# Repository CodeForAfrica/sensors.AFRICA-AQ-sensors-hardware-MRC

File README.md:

# sensors.AFRICA MRC AQ Kits Hardware

## Tools used

* Autodesk Eagle

* Fusion360

## sensors.AFRICA Stack

1. Firmware - https://github.com/CodeForAfrica/sensors.AFRICA-AQ-sensors-software
2. API - https://github.com/CodeForAfricaLabs/sensors.AFRICA-AQ-api
3. Map - https://github.com/CodeForAfrica/sensors.AFRICA-AQ-map-v2

## Documentation

The Documentation is under development.

## License

GNU General Public License v3.0

sensors.AFRICA is a citizen-science focused project by Code for Africa that seeks to address data gaps by providing low cost sensors, which people can use to measure and monitor the quality of the air, water, and environment in their communities. This web app seeks to be the public portal through which most users would discover and explore the data and intiative.

Copyright (C) 2019 Code for Africa

This program is free software: you can redistribute it and/or modify
it under the terms of the GNU General Public License as published by
the Free Software Foundation, either version 3 of the License, or
(at your option) any later version.

This program is distributed in the hope that it will be useful,
but WITHOUT ANY WARRANTY; without even the implied warranty of
MERCHANTABILITY or FITNESS FOR A PARTICULAR PURPOSE. See the
GNU General Public License for more details.

You should have received a copy of the GNU General Public License
along with this program. If not, see <https://www.gnu.org/licenses/>

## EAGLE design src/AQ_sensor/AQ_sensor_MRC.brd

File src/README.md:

# sensors.AFRICA / MRC AQ sensors hardware

This folder contains the Eagle design files for the sensors.AFRICA MRC boards.

### Folders

* **AQ_sensor** The Printed Circuit Board of the AQ kit

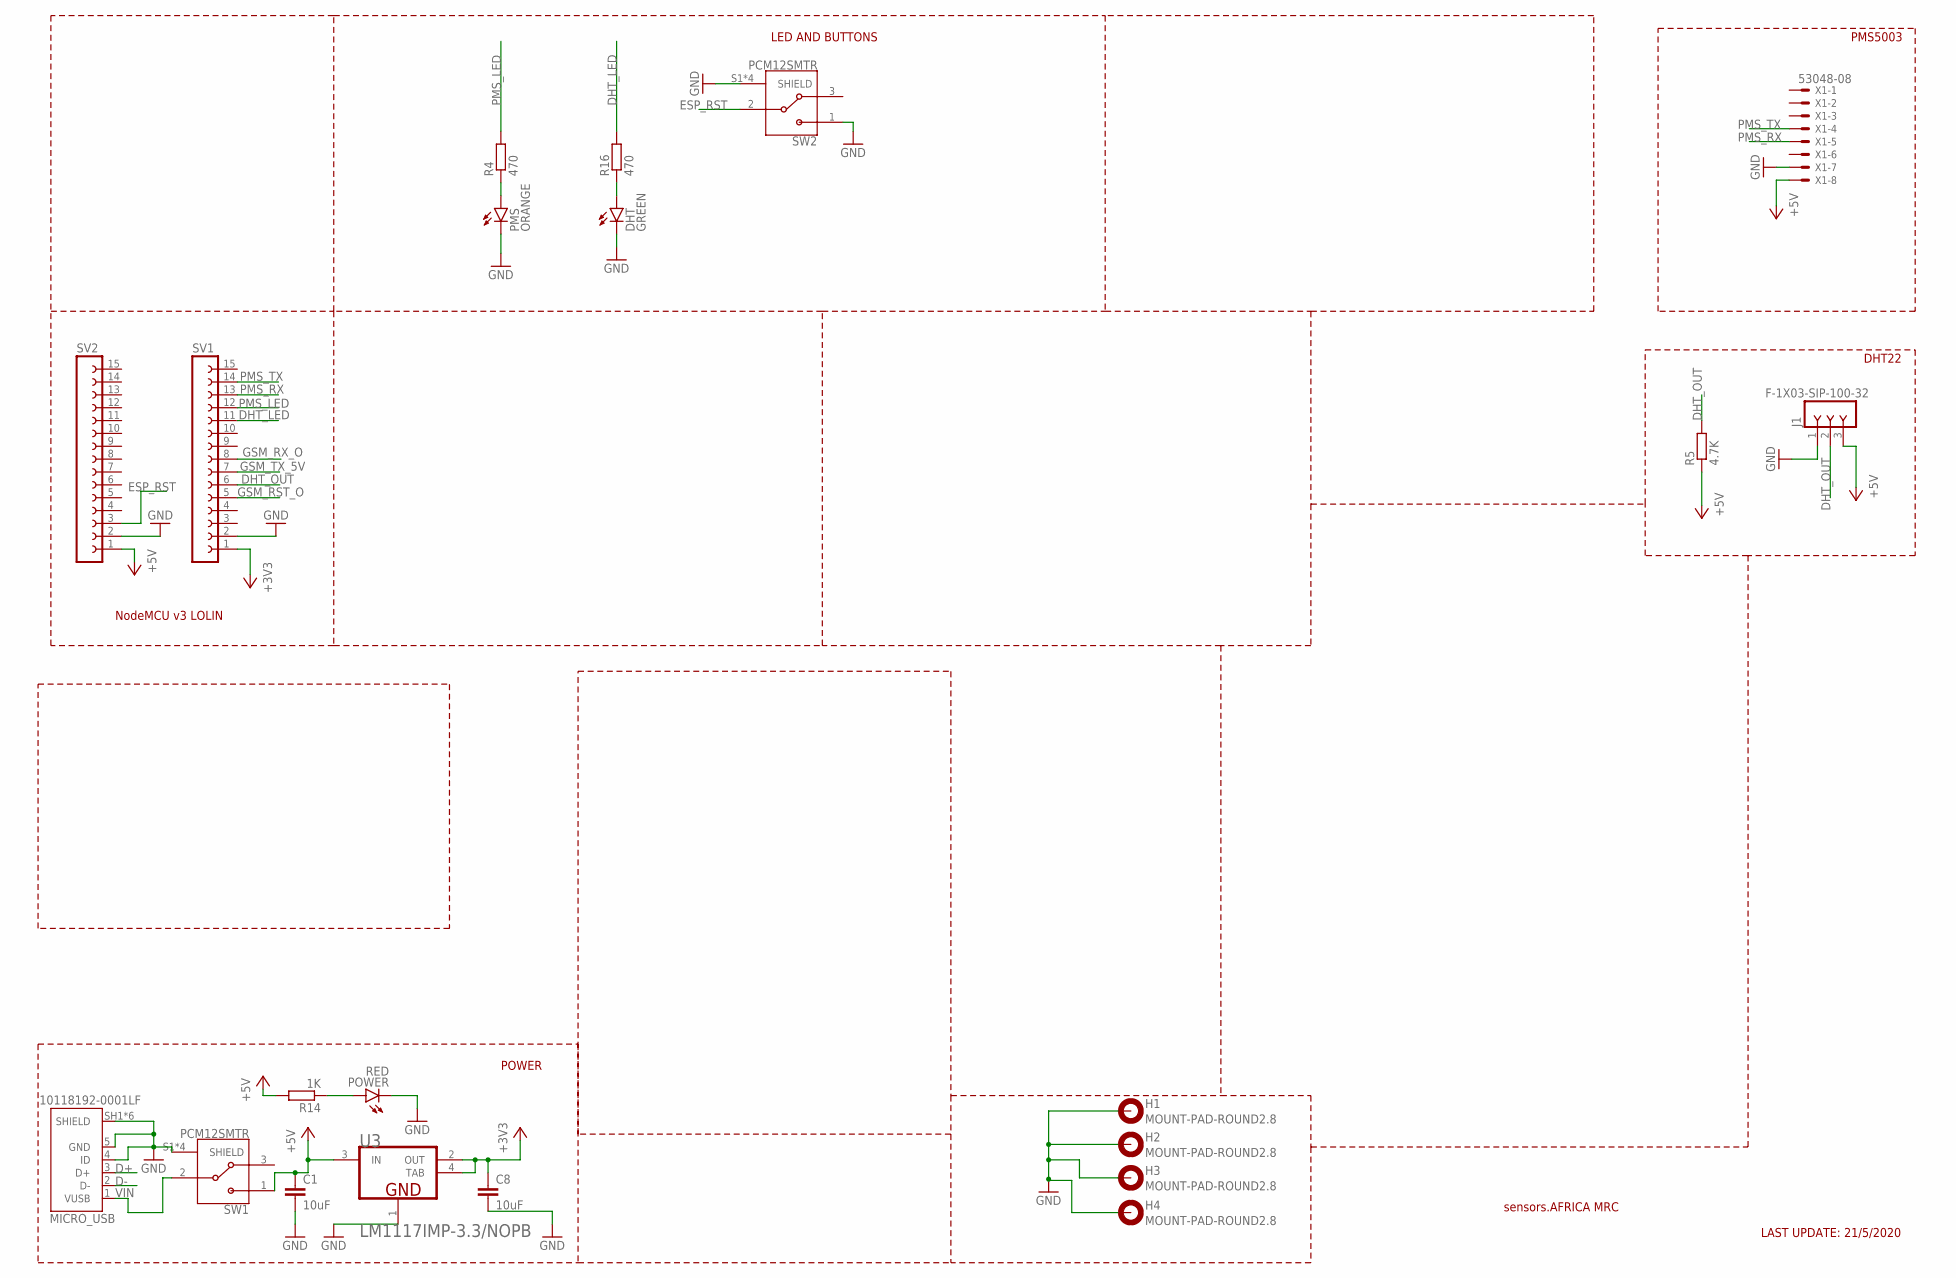
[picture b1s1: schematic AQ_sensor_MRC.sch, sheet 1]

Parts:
C1, C8: 10uF; C0603
DHT: GREEN; CHIP-LED0603
H1, H2, H3, H4: MOUNT-PAD-ROUND2.8; 2,8-PAD
J1: F-1X03-SIP-100-32; SIP-100-03-32
MICRO_USB: 10118192-0001LF; AMPHENOL_10118192-0001LF
PMS: ORANGE; CHIP-LED0603
POWER: RED; CHIP-LED0603
R4, R16: 470; R0603
R5: 4.7K; R0603
R14: 1K; R0603
SV1, SV2: FE15-1; FE15
SW1, SW2: PCM12SMTR; SW_PCM12SMTR
U3: TEXAS_INSTRUMENTS_LM1117IMP-3.3-NOPBTEXAS_INSTRUM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; TEXAS_INSTRUMENTS_LM1117IMP-3.3-NOPB_0
X1: 53048-08

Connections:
+3V3: C8.1, SV1.1, U3.2 (OUT), U3.4 (TAB)
+5V: C1.1, J1.3, R5.1, R14.2, SV2.1, SW1.1, U3.3 (IN), X1.8; also elsewhere on the board
D+: MICRO_USB.3 (D+)
D-: MICRO_USB.2 (D-)
DHT_LED: R16.2, SV1.11
DHT_OUT: J1.2, R5.2, SV1.6
ESP_RST: SV2.3, SW2.2
GND: C1.2, C8.2, DHT.C, H1.B2,8, H2.B2,8, H3.B2,8, H4.B2,8, J1.1, MICRO_USB.4 (ID), MICRO_USB.5 (GND), MICRO_USB.SH1 (SHIELD), MICRO_USB.SH2 (SHIELD), MICRO_USB.SH3 (SHIELD), MICRO_USB.SH4 (SHIELD), MICRO_USB.SH5 (SHIELD), MICRO_USB.SH6 (SHIELD), PMS.C, POWER.C, SV1.2, SV2.2, SW1.S1 (SHIELD), SW1.S2 (SHIELD), SW1.S3 (SHIELD), SW1.S4 (SHIELD), SW2.1, SW2.S1 (SHIELD), SW2.S2 (SHIELD), SW2.S3 (SHIELD), SW2.S4 (SHIELD), U3.1 (GND), X1.7; also elsewhere on the board
GSM_RST_O: SV1.5; also elsewhere on the board
GSM_RX_O: SV1.8; also elsewhere on the board
GSM_TX_5V: SV1.7; also elsewhere on the board
unnamed: PMS.A, R4.1
unnamed: POWER.A, R14.1
unnamed: DHT.A, R16.1
PMS_LED: R4.2, SV1.12
PMS_RX: SV1.13, X1.5
PMS_TX: SV1.14, X1.4
VIN: MICRO_USB.1 (VUSB), SW1.2

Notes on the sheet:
sensors.AFRICA MRC
LAST UPDATE: 21/5/2020
LED AND BUTTONS
PMS5003
DHT22
NodeMCU v3 LOLIN
POWER

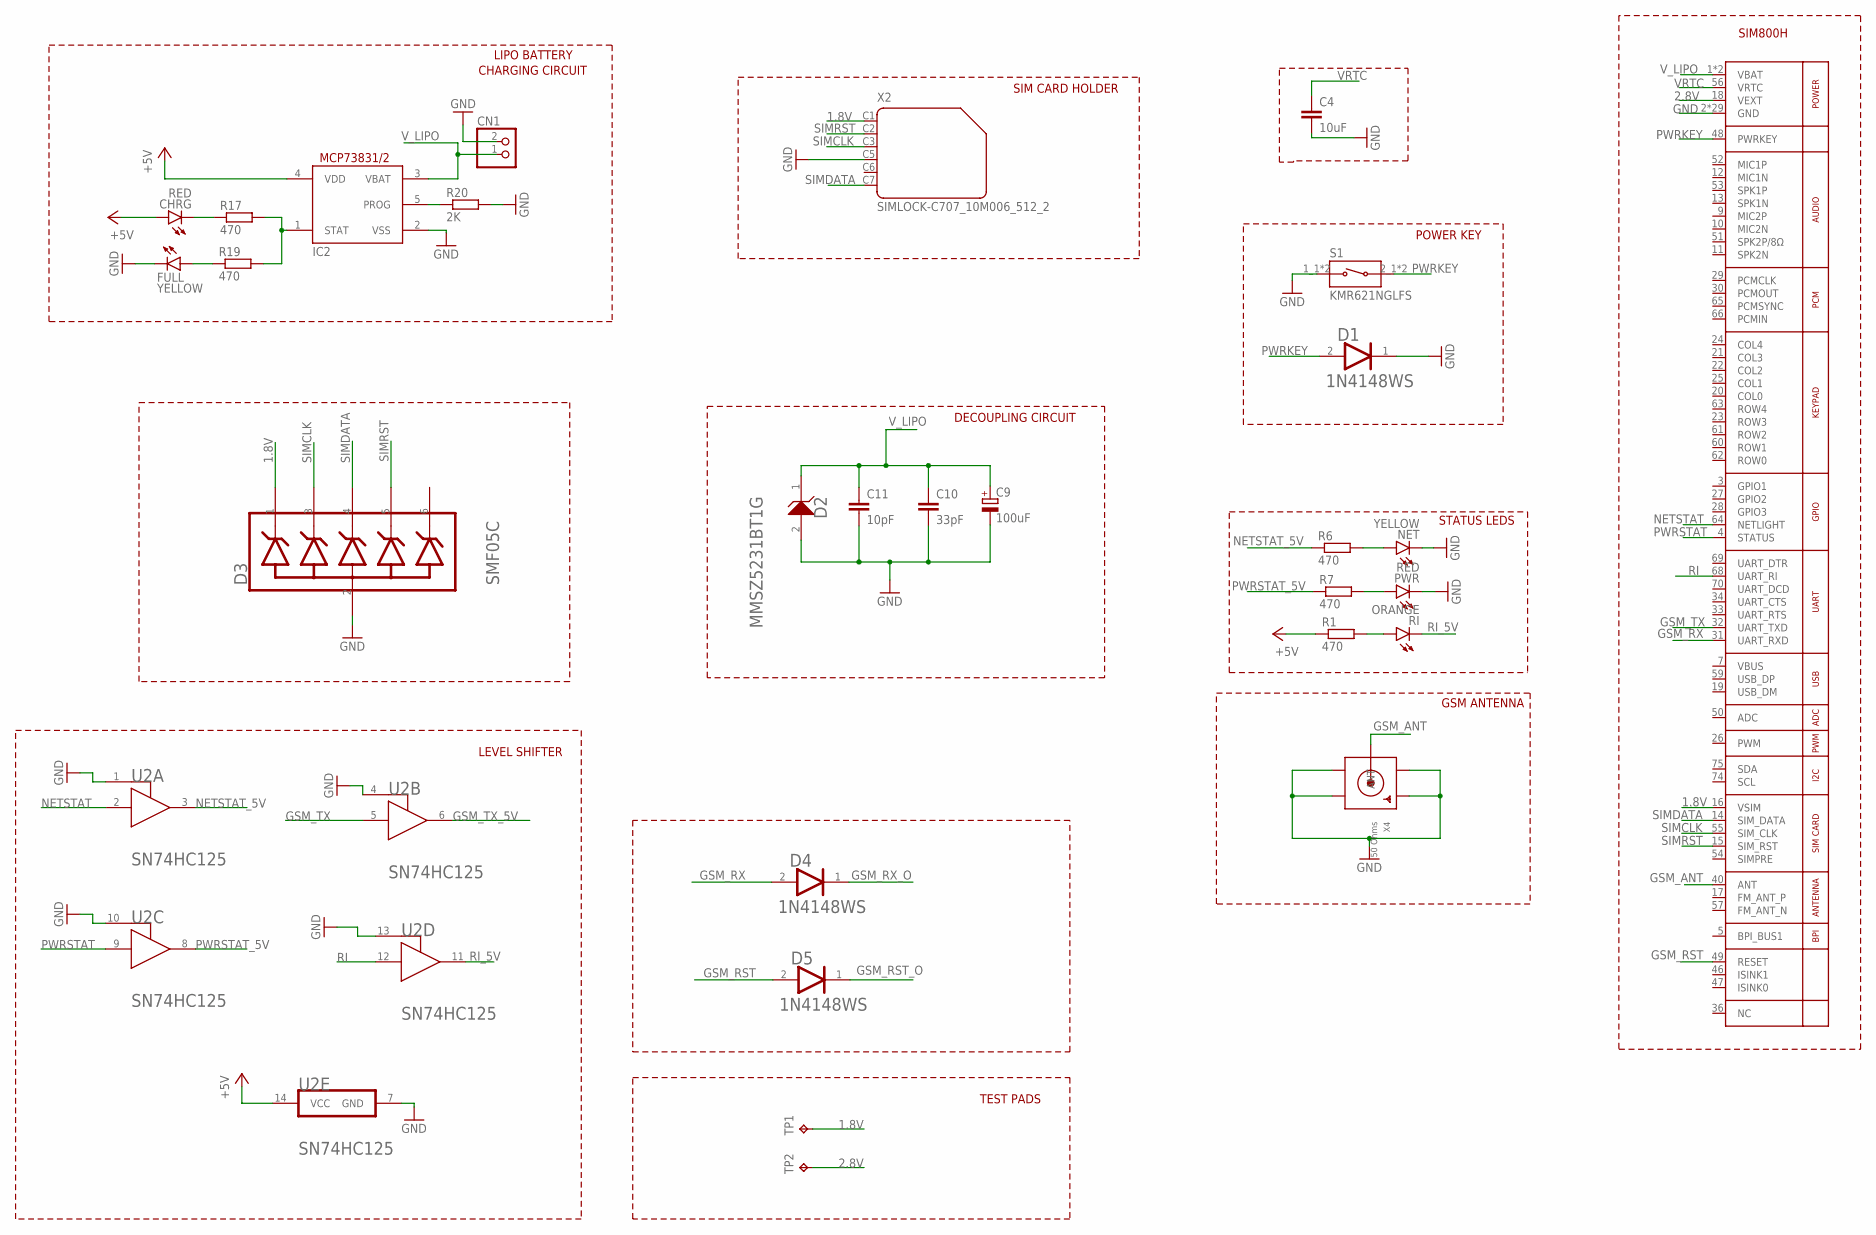
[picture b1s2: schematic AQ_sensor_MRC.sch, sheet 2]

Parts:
C4: 10uF; C0603
C9: 100uF; PANASONIC_D
C10: 33pF; C0603
C11: 10pF; C0603
CHRG: RED; CHIP-LED0603
CN1: JST_2PIN-SMT-RA; JST-PH-2-SMT-RA
D1, D4, D5: ON_SEMI_1N4148WSON_SEMI_1N4148WS_0_0; ON_SEMI_1N4148WS_0
D2: ON_SEMICONDUCTOR_MMSZ5231BT1GON_SEMICONDUCTOR_MMS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; ON_SEMICONDUCTOR_MMSZ5231BT1G_0
D3: SEMTECH_SMF05CSEMTECH_SMF05C_0_0; SEMTECH_SMF05C_0
FULL: YELLOW; CHIP-LED0603
IC2: MCP73831/OT; SOT23-5L
NET: YELLOW; CHIP-LED0603
PWR: RED; CHIP-LED0603
R1, R6, R7, R17, R19: 470; R0603
R20: 2K; R0603
RI: ORANGE; CHIP-LED0603
S1: KMR621NGLFS; SW_KMR621NGLFS
TP1, TP2: TPB1,27; B1,27
U1: GSM_SIM800L; SIM800L
U2: TEXAS_INSTRUMENTS_SN74HC125TEXAS_INSTRUMENTS_SN74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; TEXAS_INSTRUMENTS_SN74HC125_0
X2: SIMLOCK-C707_10M006_512_2; C707_10M006_512_2
X4: 50 Ohms; SMA_EDGELAUNCH_UFL

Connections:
1.8V: D3.1 (1_CATHODE), TP1.TP, U1.16 (VSIM), X2.C1 (1)
2.8V: TP2.TP, U1.18 (VEXT)
+5V: CHRG.A, IC2.4 (VDD), R1.1, U2.14 (VCC); also elsewhere on the board
GND: C4.2, C9.-, C10.2, C11.2, CN1.2 (1), D1.1 (CATHODE), D2.2 (A), D3.2 (ANODE), FULL.C, IC2.2 (VSS), NET.C, PWR.C, R20.2, S1.1_1 (1), S1.1_2 (1), U1.2 (GND), U1.6 (GND), U1.8 (GND), U1.35 (GND), U1.37 (GND), U1.38 (GND), U1.39 (GND), U1.41 (GND), U1.43 (GND), U1.44 (GND), U1.45 (GND), U1.58 (GND), U1.67 (GND), U1.71 (GND), U1.72 (GND), U1.73 (GND), U1.76 (GND), U1.77 (GND), U1.78 (GND), U1.79 (GND), U1.80 (GND), U1.81 (GND), U1.82 (GND), U1.83 (GND), U1.84 (GND), U1.85 (GND), U1.86 (GND), U1.87 (GND), U1.88 (GND), U2.1 (1_!OE!), U2.4 (4_!OE!), U2.7 (GND), U2.10 (2_!OE!), U2.13 (3_!OE!), X2.C5 (4), X4.GND@1 (GND1), X4.GND@2 (GND2), X4.GND@3 (GND3), X4.GND@4 (GND4); also elsewhere on the board
GSM_ANT: U1.40 (ANT), X4.P (ANT)
GSM_RST: D5.2 (ANODE), U1.49 (RESET)
GSM_RST_O: D5.1 (CATHODE); also elsewhere on the board
GSM_RX: D4.2 (ANODE), U1.31 (UART_RXD)
GSM_RX_O: D4.1 (CATHODE); also elsewhere on the board
GSM_TX: U1.32 (UART_TXD), U2.5 (2A)
GSM_TX_5V: U2.6 (2Y); also elsewhere on the board
unnamed: CHRG.C, R17.1
unnamed: IC2.1 (STAT), R17.2, R19.2
unnamed: NET.A, R6.2
unnamed: PWR.A, R7.2
unnamed: FULL.A, R19.1
unnamed: IC2.5 (PROG), R20.1
unnamed: R1.2, RI.A
NETSTAT: U1.64 (NETLIGHT), U2.2 (1A)
NETSTAT_5V: R6.1, U2.3 (1Y)
PWRKEY: D1.2 (ANODE), S1.2_1 (2), S1.2_2 (2), U1.48 (PWRKEY)
PWRSTAT: U1.4 (STATUS), U2.9 (3A)
PWRSTAT_5V: R7.1, U2.8 (3Y)
RI: U1.68 (UART_RI), U2.12 (4A)
RI_5V: RI.C, U2.11 (4Y)
SIMCLK: D3.3 (2_CATHODE), U1.55 (SIM_CLK), X2.C3 (3)
SIMDATA: D3.4 (3_CATHODE), U1.14 (SIM_DATA), X2.C7 (6)
SIMRST: D3.5 (4_CATHODE), U1.15 (SIM_RST), X2.C2 (2)
VBUS: U1.7 (VBUS)
VRTC: C4.1, U1.56 (VRTC)
V_LIPO: C9.+, C10.1, C11.1, CN1.1 (2), D2.1 (K), IC2.3 (VBAT), U1.1 (VBAT), U1.42 (VBAT)

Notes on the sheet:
SIM800H
POWER KEY
STATUS LEDS
SIM CARD HOLDER
CHARGING CIRCUIT
LIPO BATTERY
GSM ANTENNA
TEST PADS
LEVEL SHIFTER
DECOUPLING CIRCUIT

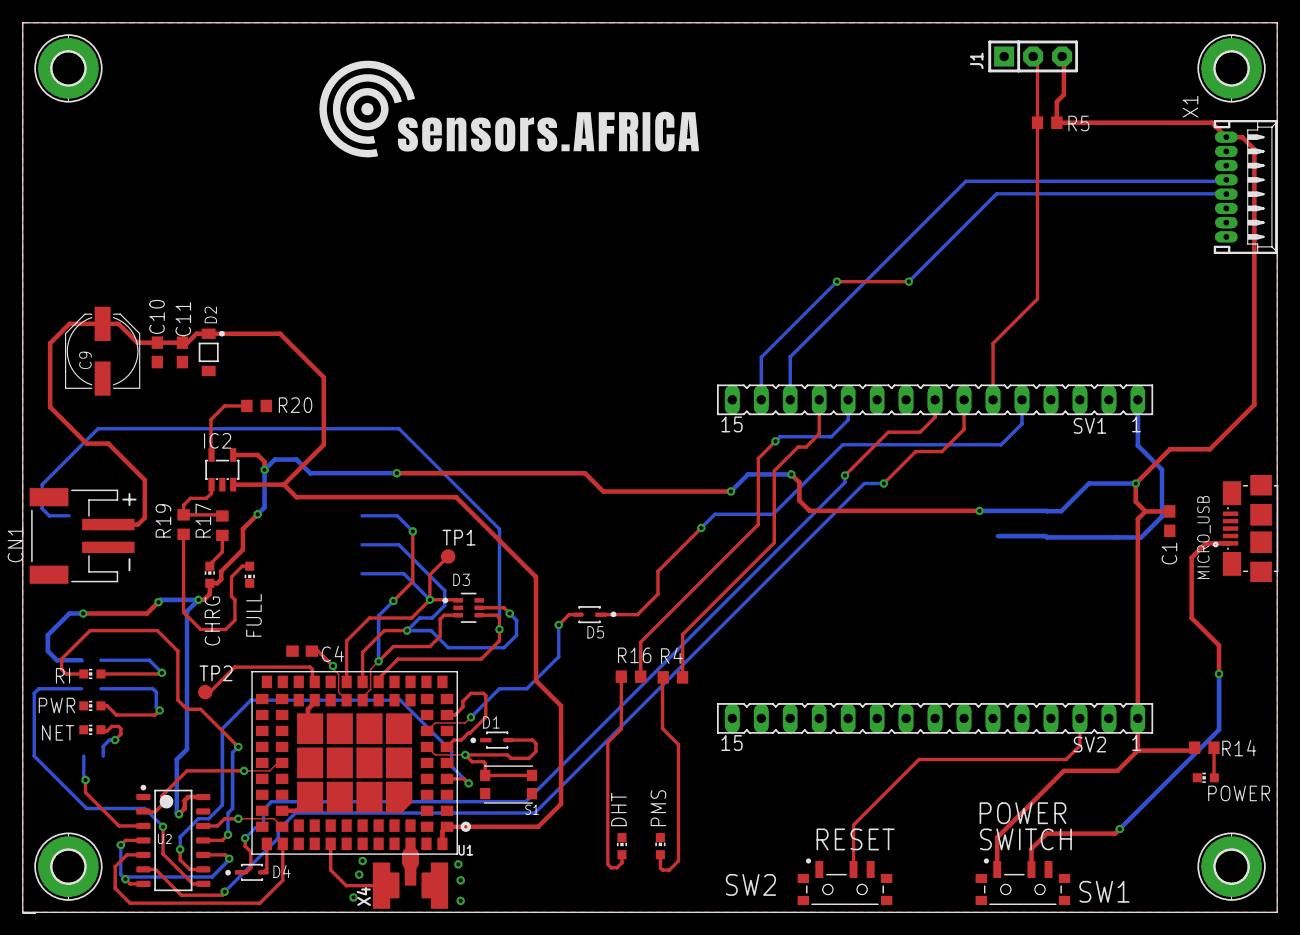
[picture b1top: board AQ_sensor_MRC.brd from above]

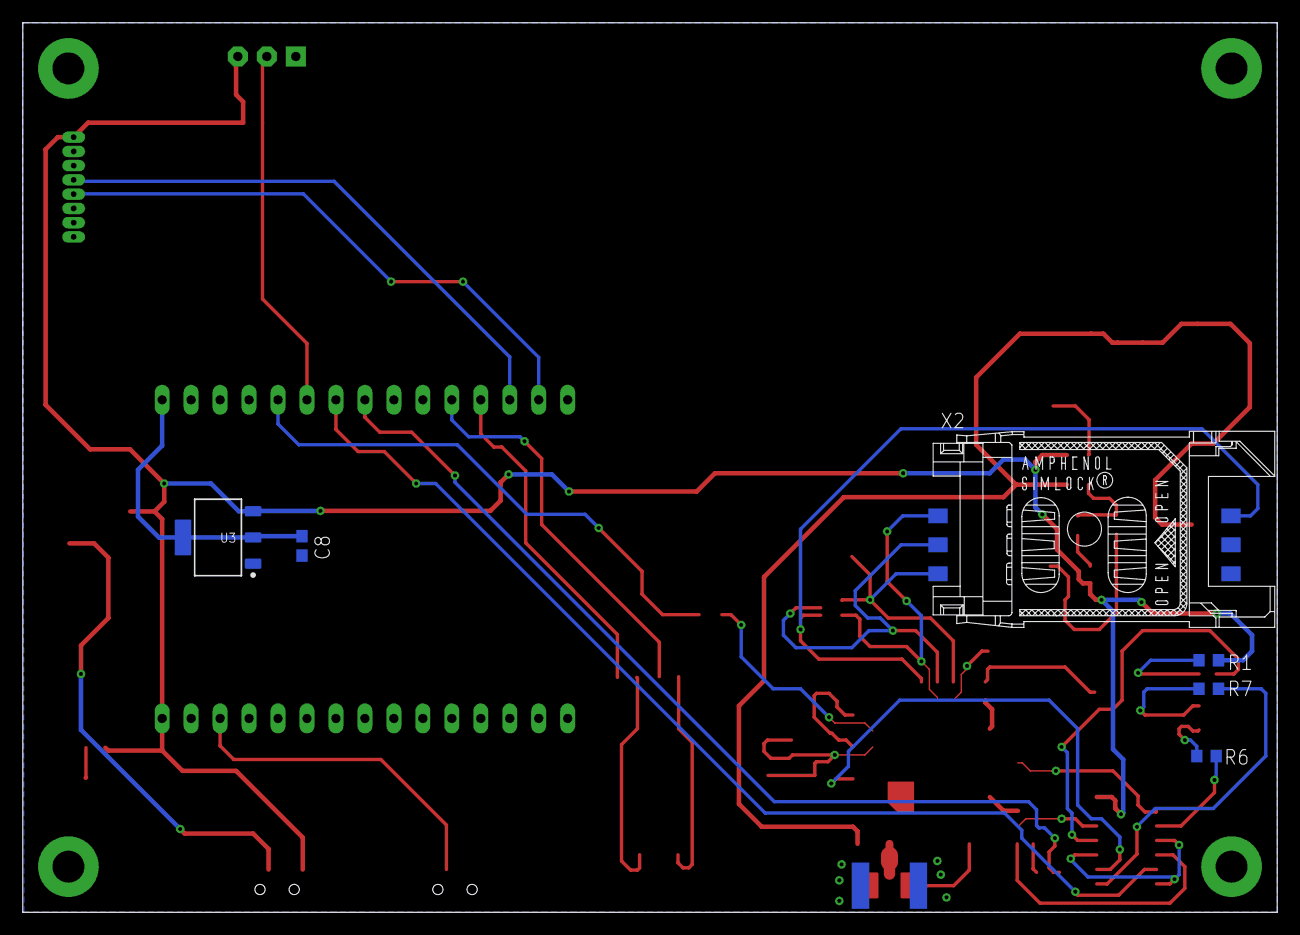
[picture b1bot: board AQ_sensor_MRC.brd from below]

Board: 2 copper layers, 110.0 x 78.0 mm, 50 parts (6 on the bottom side), 41 nets.

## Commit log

2020-11-10 MRC PCB design files
2020-11-13 created manufacturing files
2020-11-13 created managed library
2020-11-13 Added Managed library to design
2020-11-16 updated layout image
2020-11-16 Modifed RI LED connection
2020-11-16 Added ground vias
2020-11-19 Updated managed library and added 3D models
